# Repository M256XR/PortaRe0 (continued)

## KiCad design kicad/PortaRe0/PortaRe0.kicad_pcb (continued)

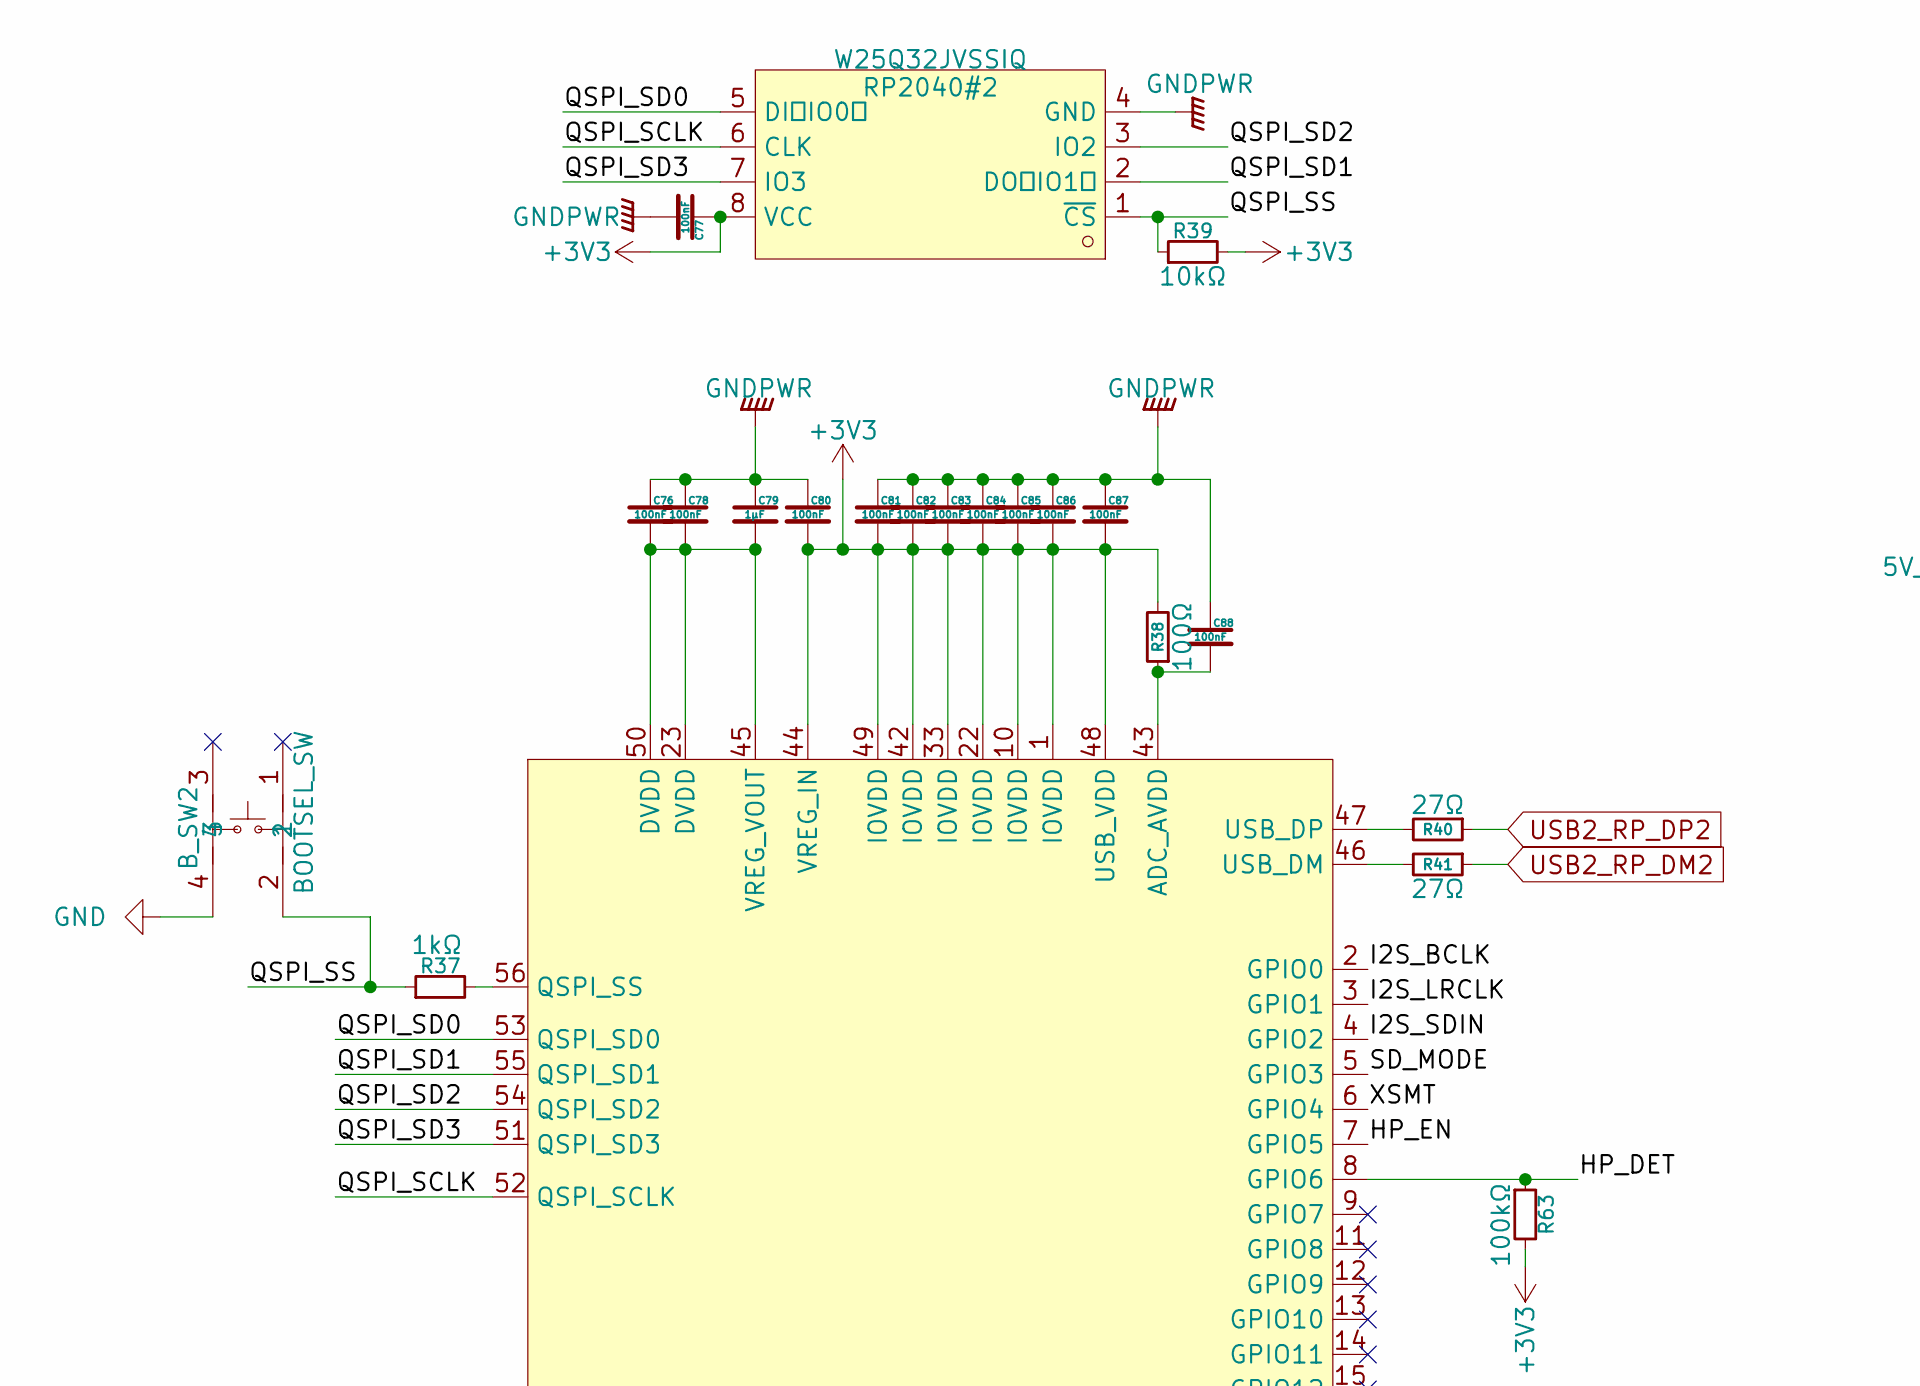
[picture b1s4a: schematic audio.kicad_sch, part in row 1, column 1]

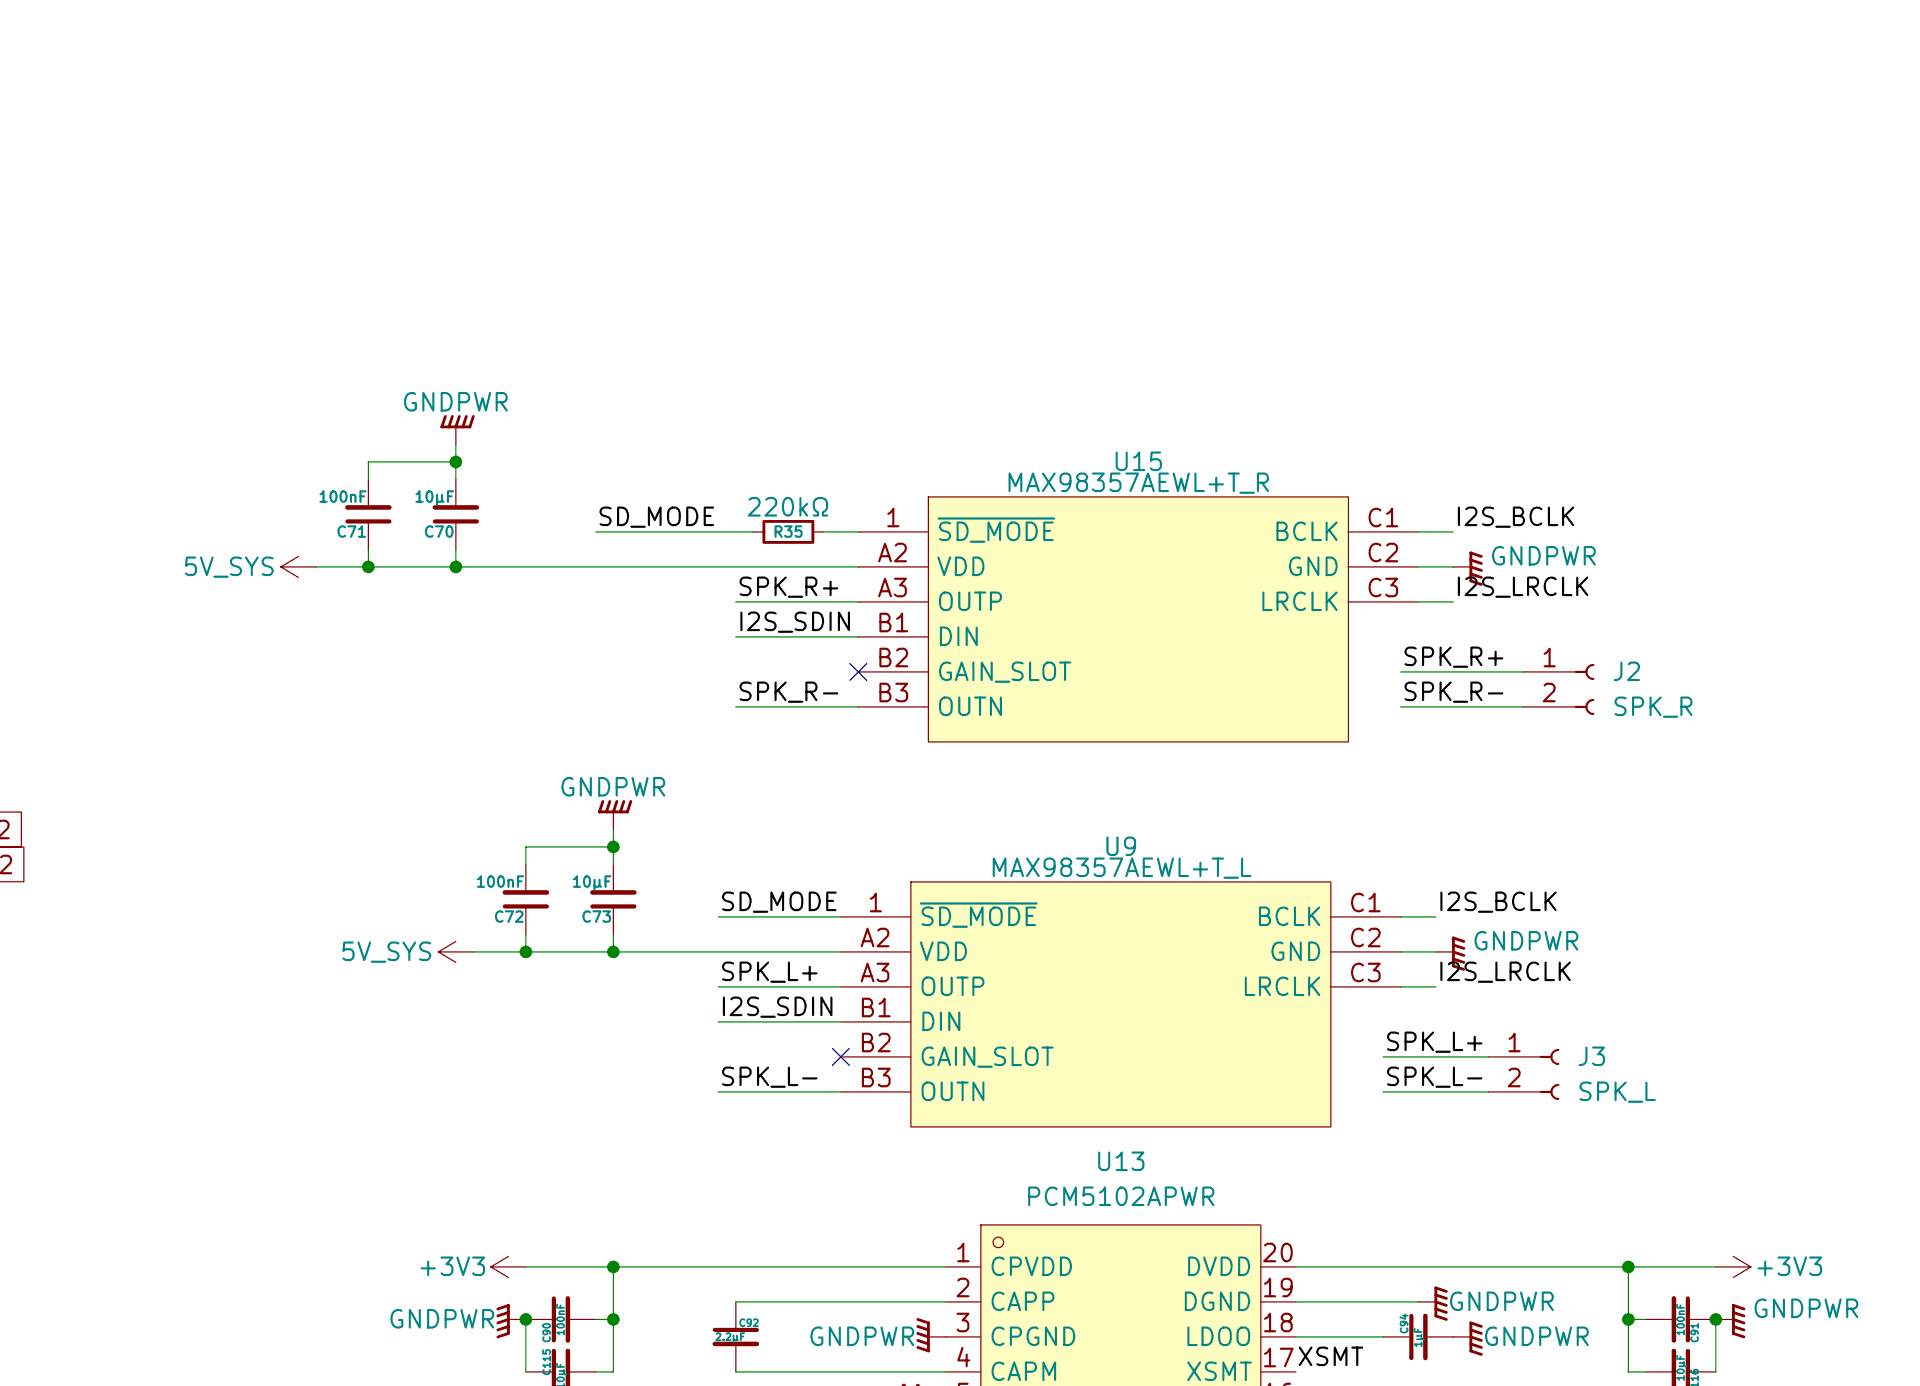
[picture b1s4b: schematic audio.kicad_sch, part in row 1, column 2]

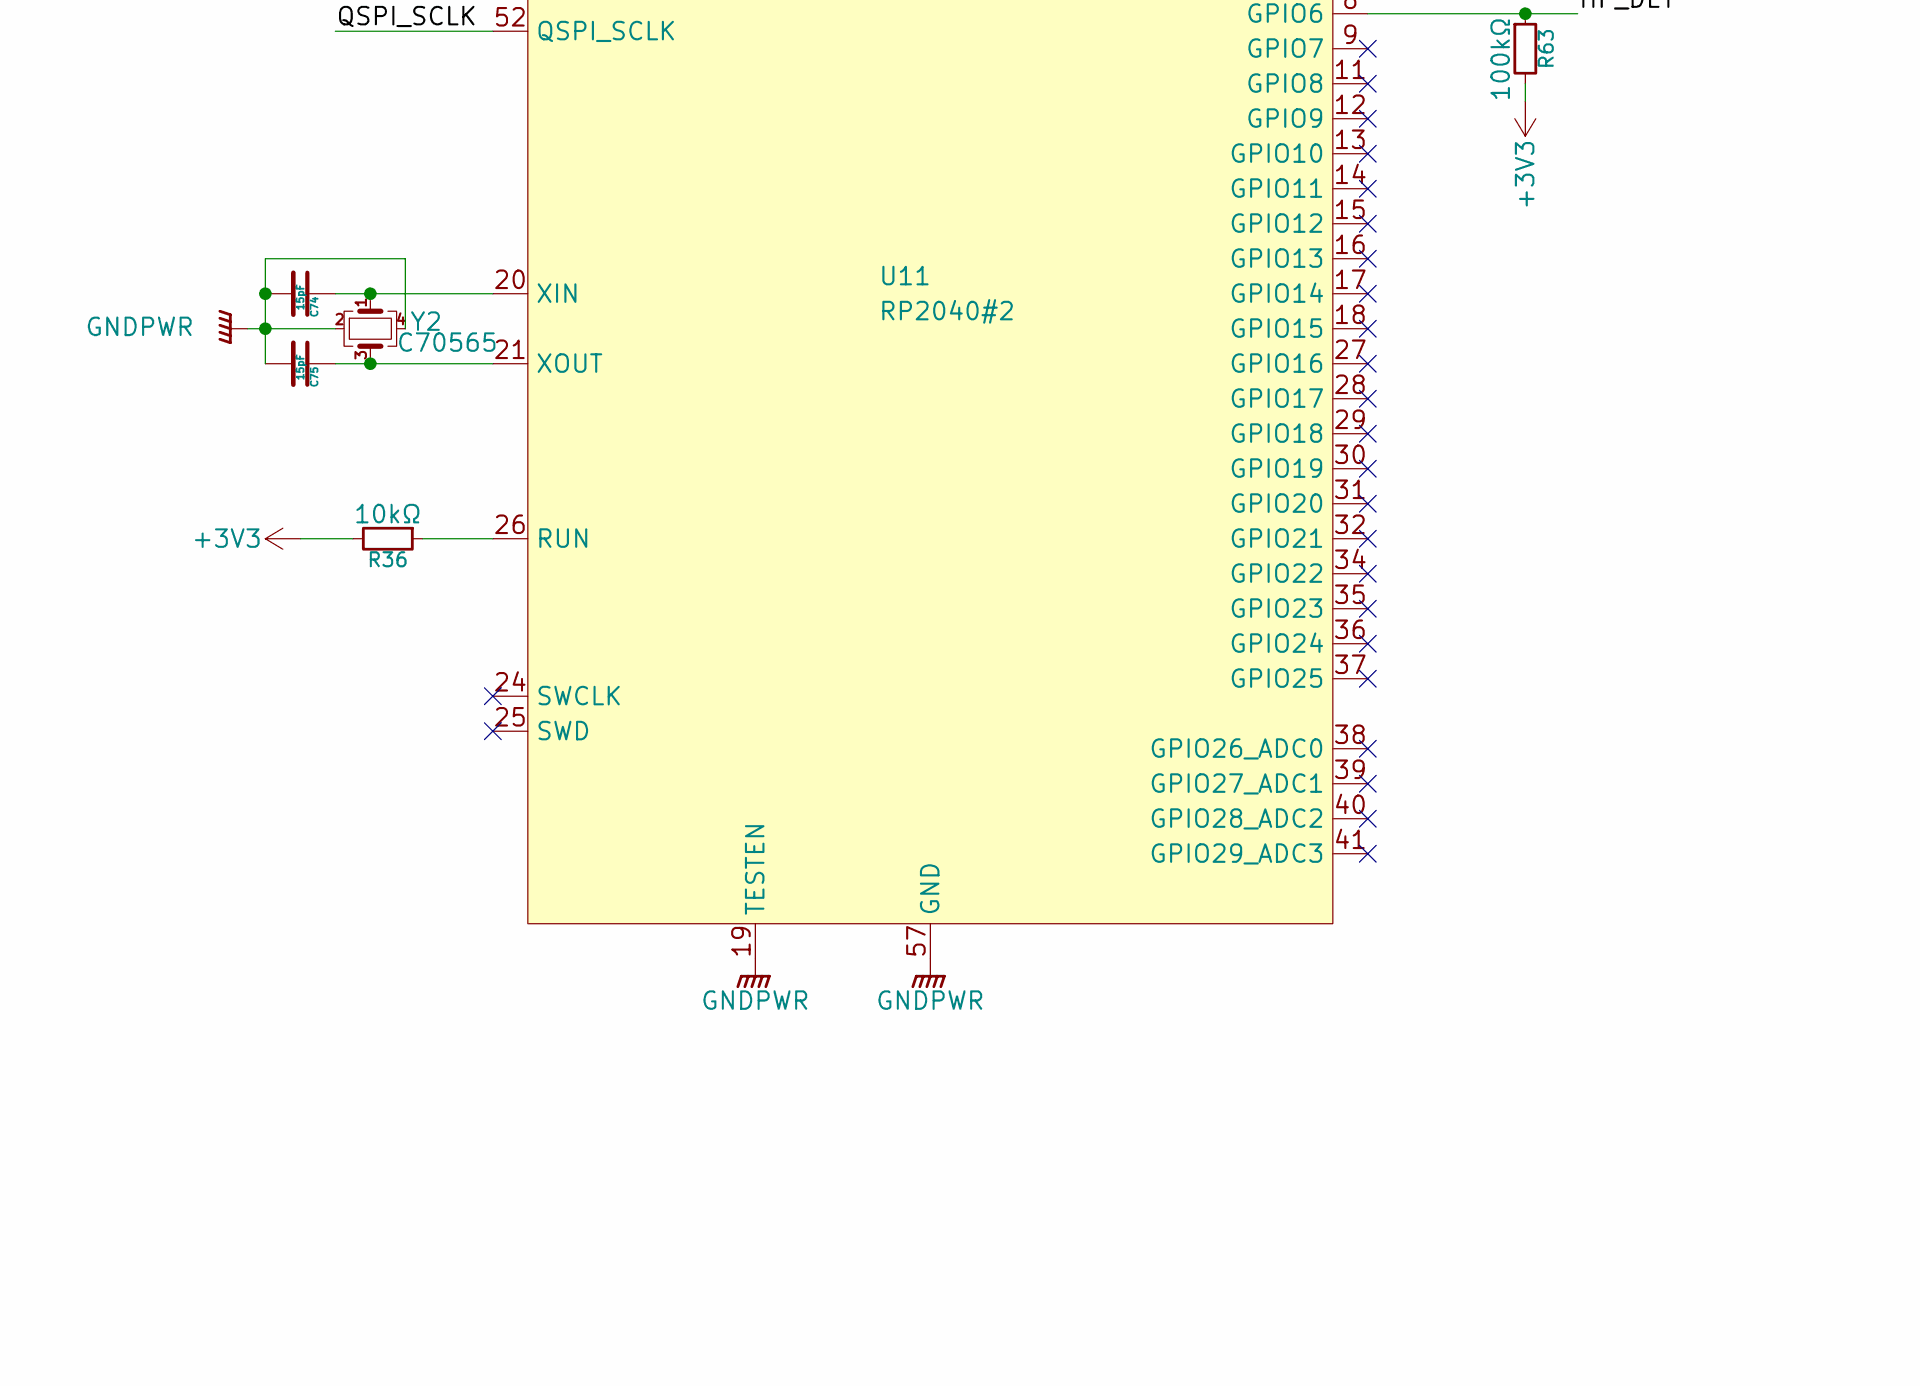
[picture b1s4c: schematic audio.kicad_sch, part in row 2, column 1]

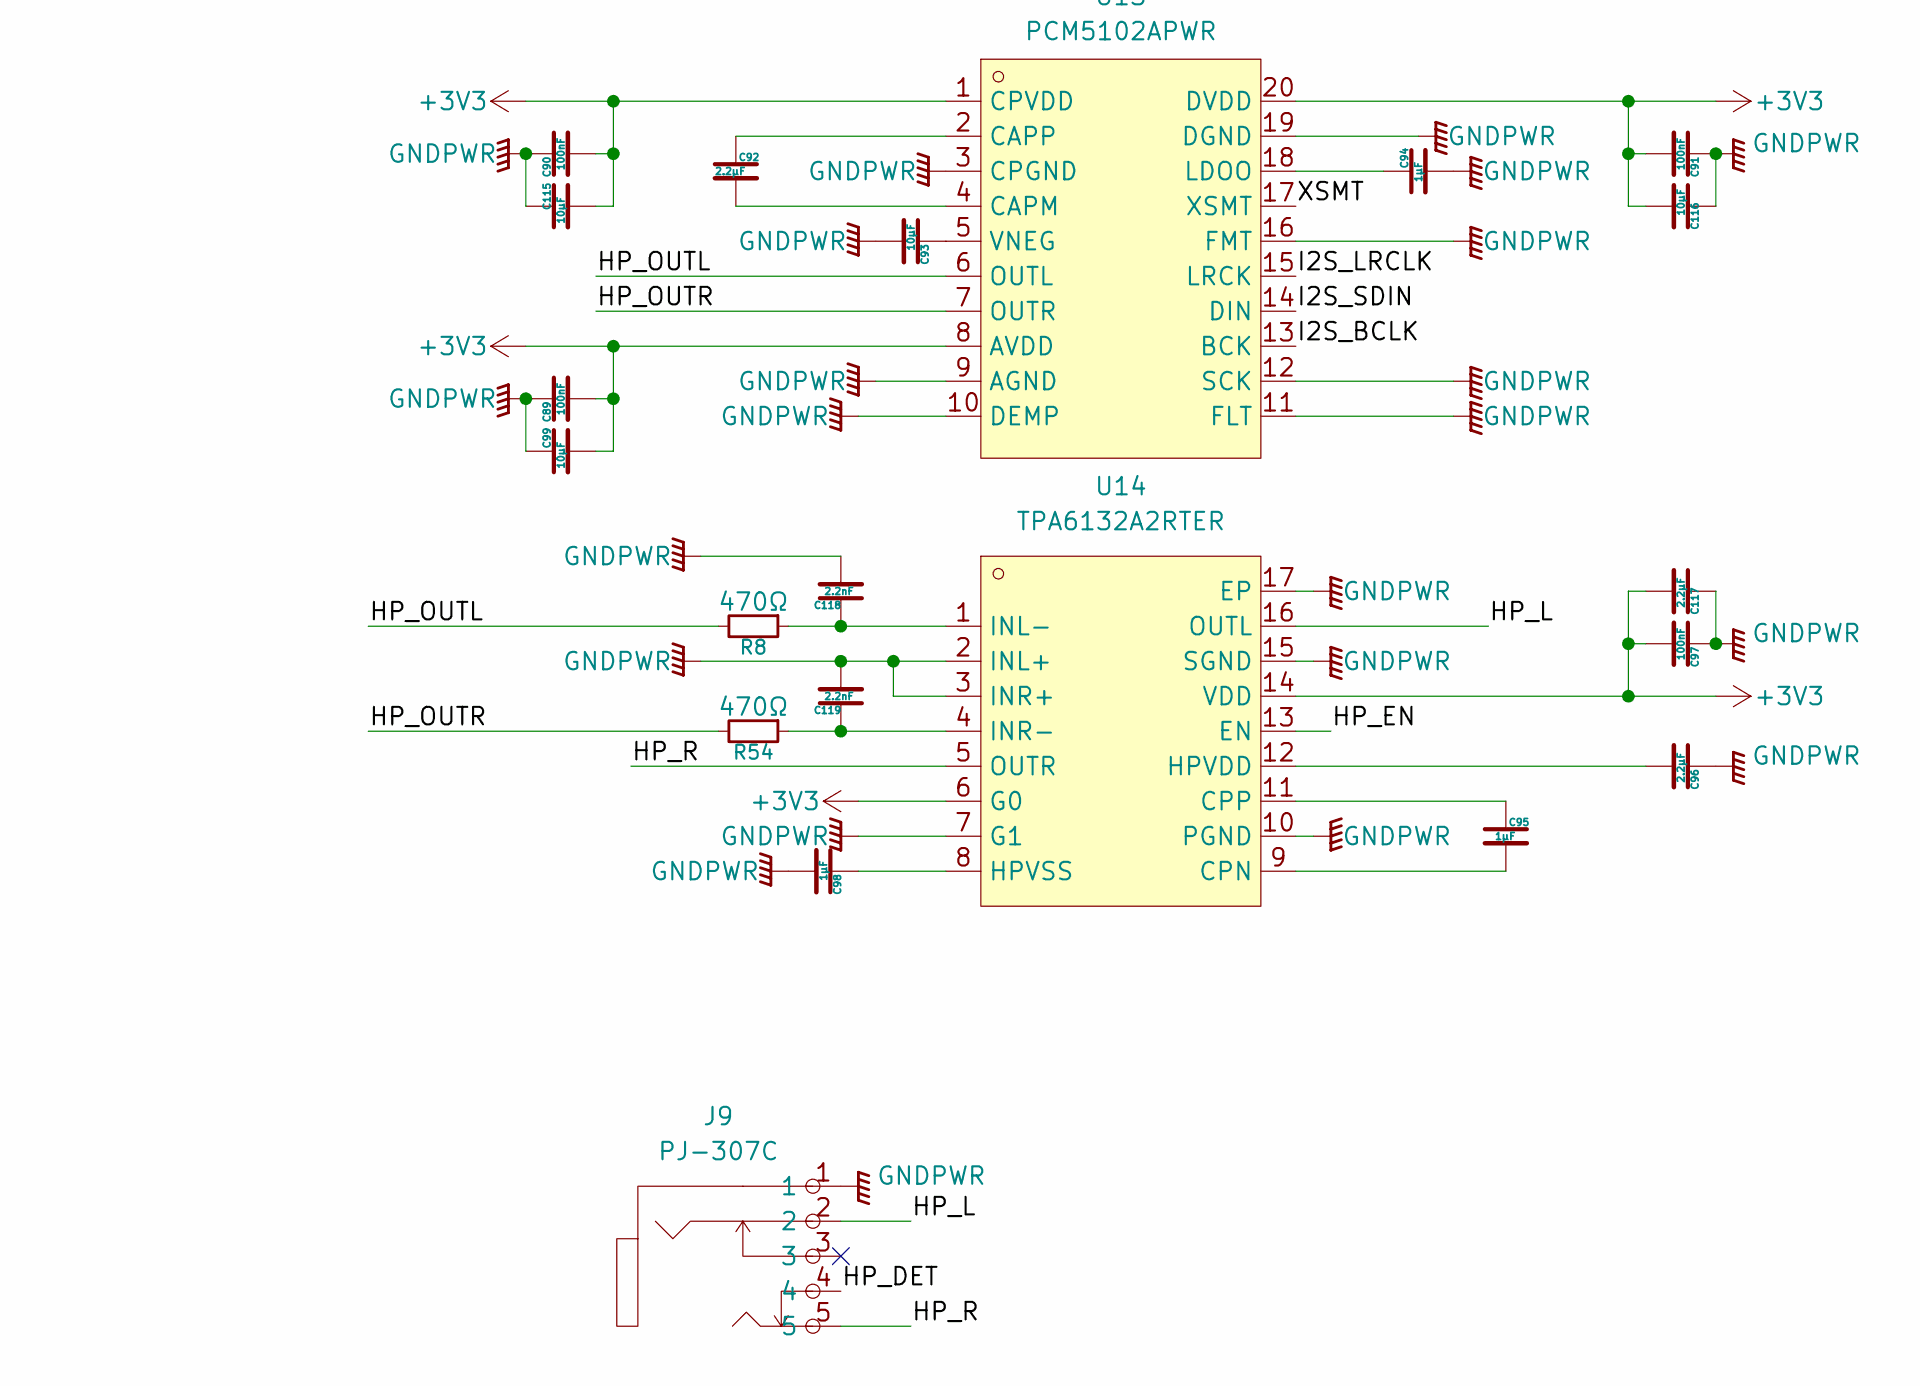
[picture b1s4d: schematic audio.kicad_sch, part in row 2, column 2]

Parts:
B_SW2: BOOTSEL_SW; KEY-SMD_4P-L4.2-W3.2-P2.20-LS4.6; LCSC Part C115360
C70, C73: 10μF; C_0603_1608Metric
C71, C72, C76, C77, C78, C80, C81, C82, C83, C84, C85, C86, C87, C88, C89, C90, C91, C97: 100nF; C_0402_1005Metric
C74, C75: 15pF; C_0402_1005Metric
C79, C94, C95, C98: 1μF; C_0402_1005Metric
C92, C96, C117: 2.2μF; C_0402_1005Metric
C93, C99, C115, C116: 10μF; C_0402_1005Metric
C118, C119: 2.2nF; C_0402_1005Metric
J2: SPK_R; CONN-TH_S2B-PH-K-S-LF-SN
J3: SPK_L; CONN-TH_S2B-PH-K-S-LF-SN
J9: PJ-307C; AUDIO-TH_PJ307C; LCSC Part C16684
R8, R54: 470Ω; R_0402_1005Metric
R35: 220kΩ; R_0603_1608Metric
R36, R39: 10kΩ; R_0402_1005Metric
R37: 1kΩ; R_0402_1005Metric
R38: 100Ω; R_0402_1005Metric
R40, R41: 27Ω; R_0603_1608Metric
R63: 100kΩ; R_0402_1005Metric
RP2040#2: W25Q32JVSSIQ; SOIC-8_L5.3-W5.3-P1.27-LS8.0-BL; LCSC Part C82344
U9: MAX98357AEWL+T_L; WLP-9_L1.4-W1.3-P0.40-R3-C3-BR; LCSC Part C2682619
U11: RP2040#2; LQFN-56_L7.0-W7.0-P0.4-EP; LCSC Part C2040
U13: PCM5102APWR; TSSOP-20_L6.5-W4.4-P0.65-LS6.4-BL; LCSC Part C107671
U14: TPA6132A2RTER; WQFN-16_L3.0-W3.0-P0.50-TL-EP1.6; LCSC Part C69901
U15: MAX98357AEWL+T_R; WLP-9_L1.4-W1.3-P0.40-R3-C3-BR; LCSC Part C2682619
Y2: C70565; CRYSTAL-SMD_4P-L3.2-W2.5-BL

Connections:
5V_SYS: C70.1, C71.1, C72.1, C73.1, U9.A2 (VDD), U15.A2 (VDD); also elsewhere on the board
+3V3: C77.1, C80.2, C81.2, C82.2, C83.2, C84.2, C85.2, C86.2, C87.2, C89.2, C90.2, C91.2, C97.2, C99.2, C115.2, C116.2, C117.2, R36.2, R38.2, R39.2, R63.2, RP2040#2.8 (VCC), U11.1 (IOVDD), U11.10 (IOVDD), U11.22 (IOVDD), U11.33 (IOVDD), U11.42 (IOVDD), U11.44 (VREG_IN), U11.48 (USB_VDD), U11.49 (IOVDD), U13.1 (CPVDD), U13.8 (AVDD), U13.20 (DVDD), U14.6 (G0), U14.14 (VDD); also elsewhere on the board
/audio/HP_DET: J9.4, R63.1, U11.8 (GPIO6)
/audio/HP_EN: U11.7 (GPIO5), U14.13 (EN)
/audio/HP_L: J9.2, U14.16 (OUTL)
/audio/HP_OUTL: R8.2, U13.6 (OUTL)
/audio/HP_OUTR: R54.2, U13.7 (OUTR)
/audio/HP_R: J9.5, U14.5 (OUTR)
/audio/I2S_BCLK: U9.C1 (BCLK), U11.2 (GPIO0), U13.13 (BCK), U15.C1 (BCLK)
/audio/I2S_LRCLK: U9.C3 (LRCLK), U11.3 (GPIO1), U13.15 (LRCK), U15.C3 (LRCLK)
/audio/I2S_SDIN: U9.B1 (DIN), U11.4 (GPIO2), U13.14 (DIN), U15.B1 (DIN)
/audio/QSPI_SCLK: RP2040#2.6 (CLK), U11.52 (QSPI_SCLK)
/audio/QSPI_SD0: RP2040#2.5 (DI（IO0）), U11.53 (QSPI_SD0)
/audio/QSPI_SD1: RP2040#2.2 (DO（IO1）), U11.55 (QSPI_SD1)
/audio/QSPI_SD2: RP2040#2.3 (IO2), U11.54 (QSPI_SD2)
/audio/QSPI_SD3: RP2040#2.7 (IO3), U11.51 (QSPI_SD3)
/audio/QSPI_SS: B_SW2.2, R37.1, R39.1, RP2040#2.1 (~CS)
/audio/SD_MODE: R35.2, U9.1 (~SD_MODE), U11.5 (GPIO3)
/audio/SPK_L+: J3.1, U9.A3 (OUTP); also elsewhere on the board
/audio/SPK_L-: J3.2, U9.B3 (OUTN); also elsewhere on the board
/audio/SPK_R+: J2.1, U15.A3 (OUTP); also elsewhere on the board
/audio/SPK_R-: J2.2, U15.B3 (OUTN); also elsewhere on the board
/audio/XSMT: U11.6 (GPIO4), U13.17 (XSMT)
GND: B_SW2.4, C70.2, C71.2, C72.2, C73.2, C74.2, C75.2, C76.1, C77.2, C78.1, C79.1, C80.1, C81.1, C82.1, C83.1, C84.1, C85.1, C86.1, C87.1, C88.1, C89.1, C90.1, C91.1, C93.2, C94.2, C96.1, C97.1, C98.2, C99.1, C115.1, C116.1, C117.1, C118.2, C119.2, J9.1, RP2040#2.4 (GND), U9.C2 (GND), U11.19 (TESTEN), U11.57 (GND), U13.3 (CPGND), U13.9 (AGND), U13.10 (DEMP), U13.11 (FLT), U13.12 (SCK), U13.16 (FMT), U13.19 (DGND), U14.2 (INL+), U14.3 (INR+), U14.7 (G1), U14.10 (PGND), U14.15 (SGND), U14.17 (EP), U15.C2 (GND), Y2.2, Y2.4; also elsewhere on the board
unnamed: C88.2, R38.1, U11.43 (ADC_AVDD)
unnamed: R37.2, U11.56 (QSPI_SS)
unnamed: R36.1, U11.26 (RUN)
unnamed: R41.2, U11.46 (USB_DM)
unnamed: R40.2, U11.47 (USB_DP)
unnamed: C76.2, C78.2, C79.2, U11.23 (DVDD), U11.45 (VREG_VOUT), U11.50 (DVDD)
unnamed: C74.1, U11.20 (XIN), Y2.1
unnamed: C75.1, U11.21 (XOUT), Y2.3
unnamed: C92.2, U13.4 (CAPM)
unnamed: C92.1, U13.2 (CAPP)
unnamed: C94.1, U13.18 (LDOO)
unnamed: C93.1, U13.5 (VNEG)
unnamed: C95.2, U14.9 (CPN)
unnamed: C95.1, U14.11 (CPP)
unnamed: C96.2, U14.12 (HPVDD)
unnamed: C98.1, U14.8 (HPVSS)
unnamed: C118.1, R8.1, U14.1 (INL-)
unnamed: C119.1, R54.1, U14.4 (INR-)
unnamed: R35.1, U15.1 (~SD_MODE)
USB2_RP_DM2: R41.1; also elsewhere on the board
USB2_RP_DP2: R40.1; also elsewhere on the board

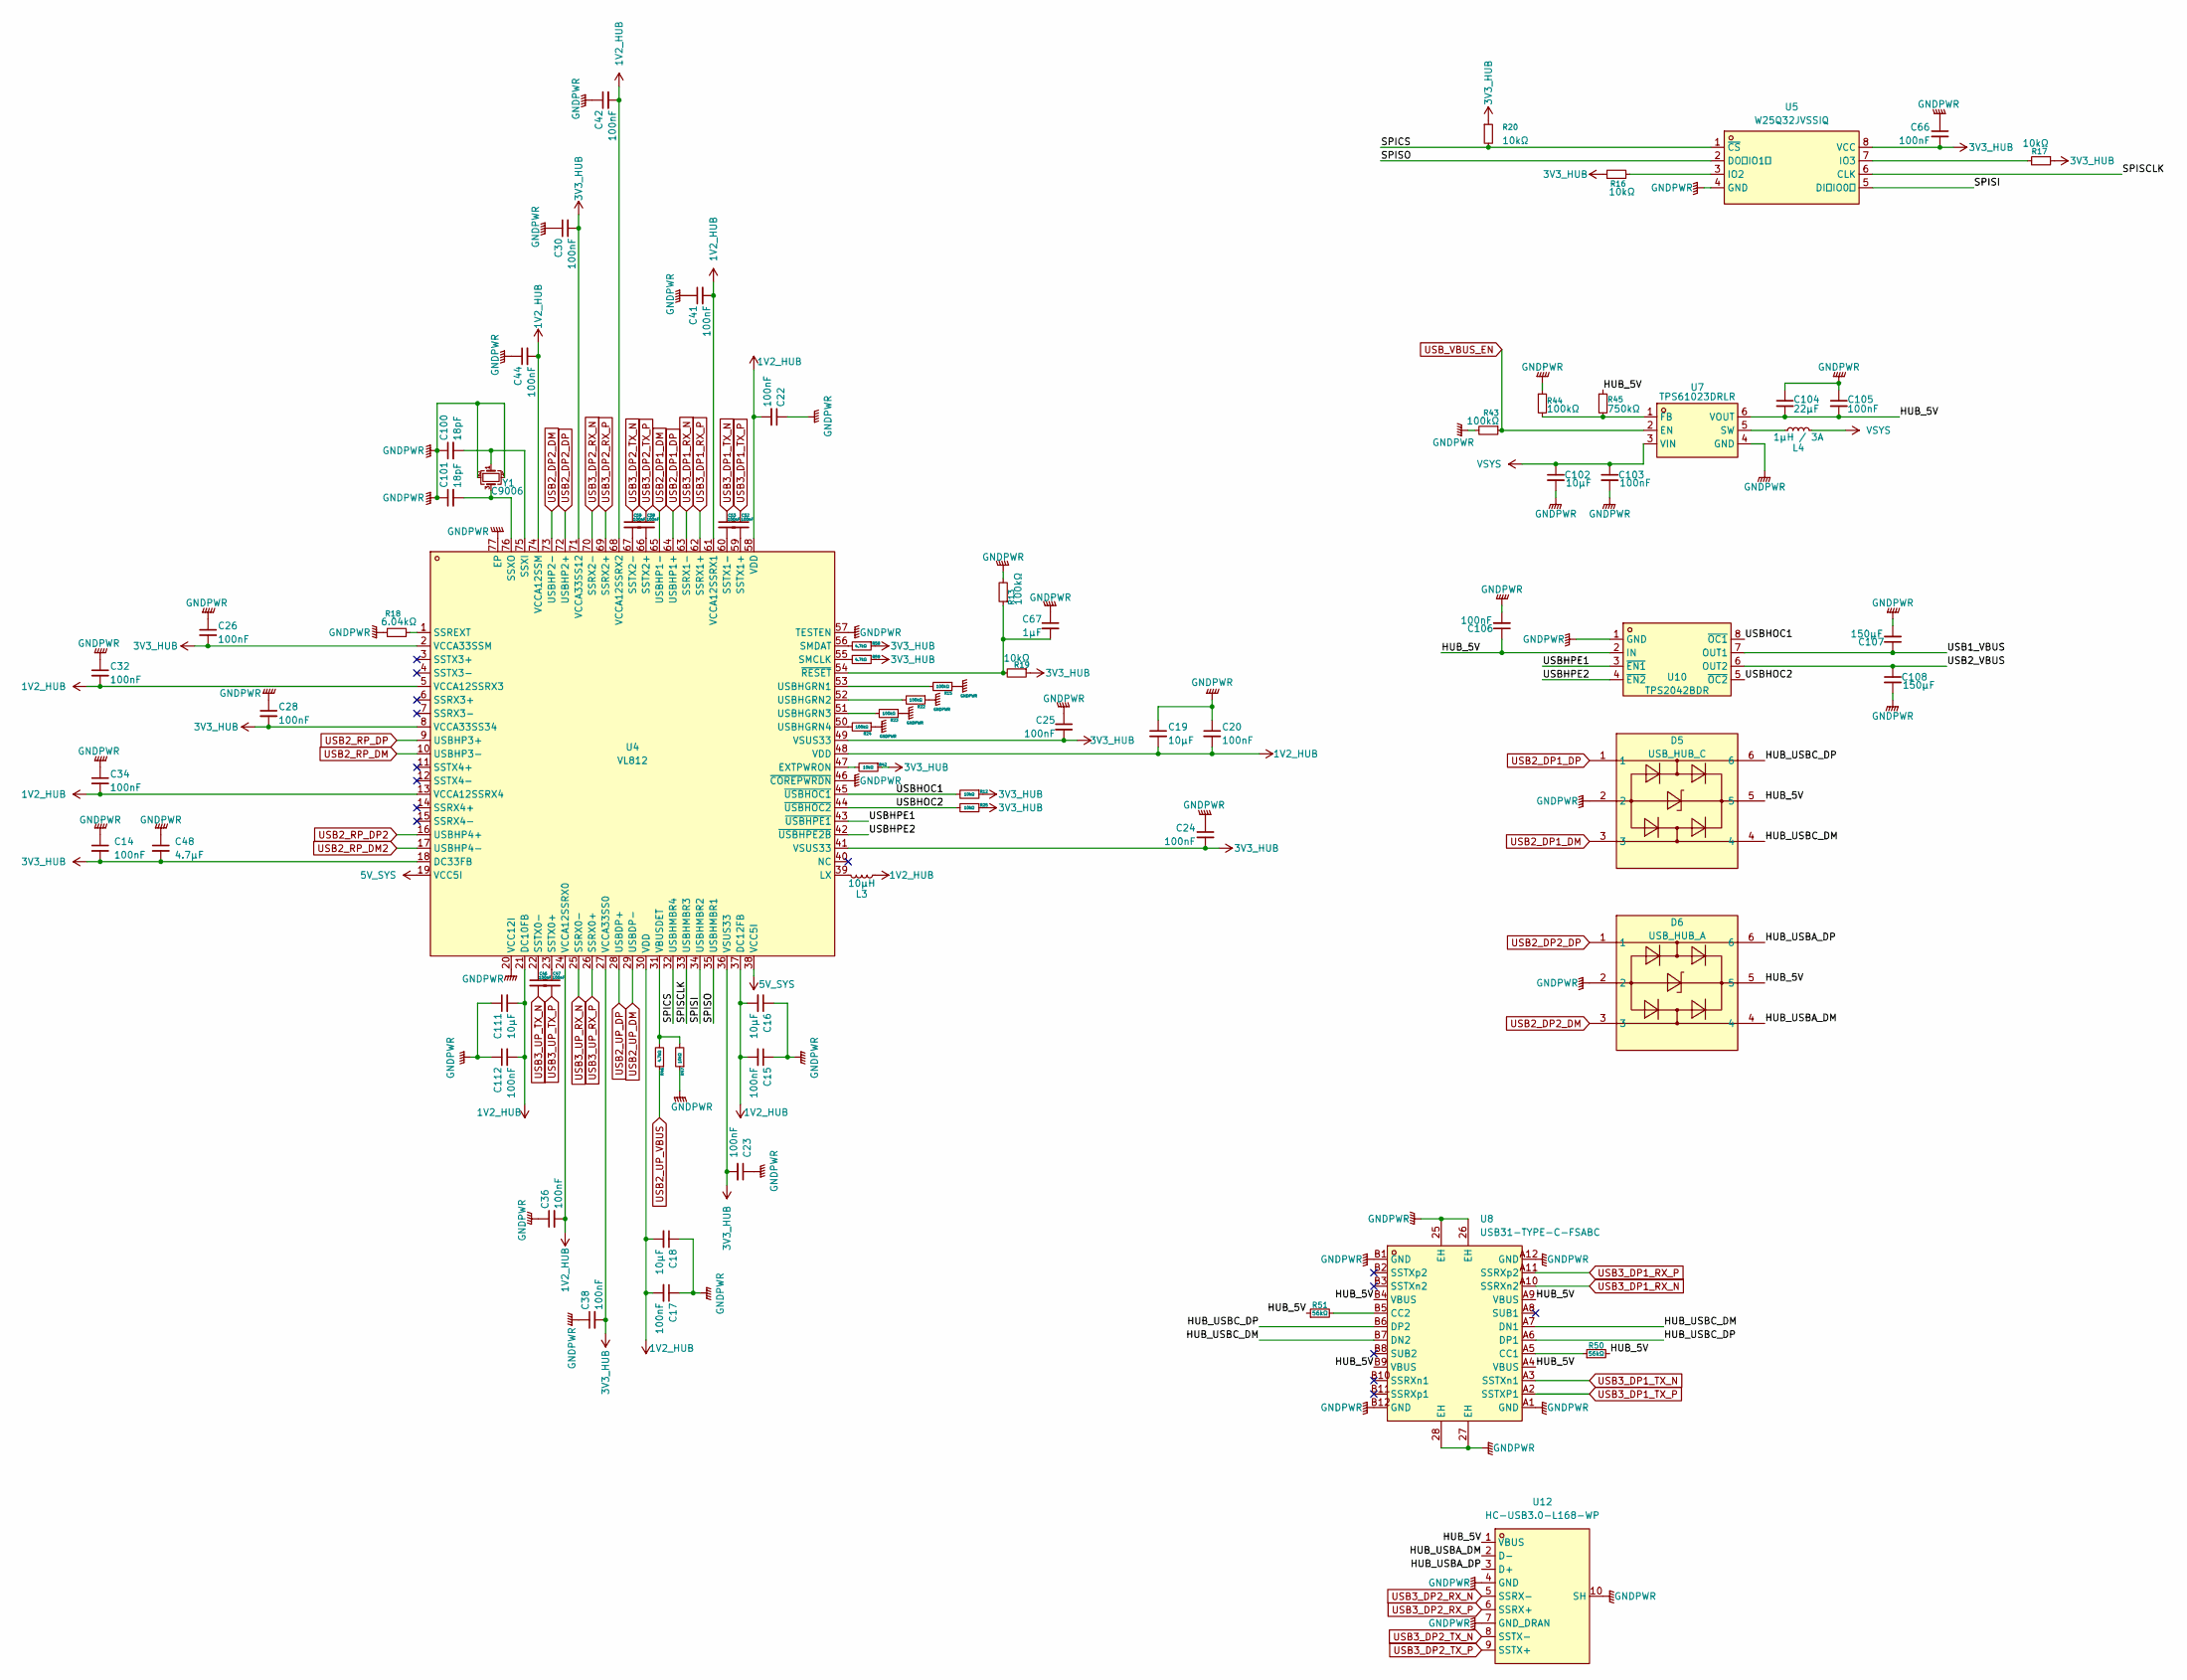
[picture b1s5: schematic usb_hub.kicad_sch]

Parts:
C14, C15, C17, C20, C22, C23, C24, C25, C26, C28, C30, C32, C34, C36, C38, C41, C42, C44, C46, C47, C52, C53, C58, C59, C66, C103, C105, C106, C112: 100nF; C_0402_1005Metric
C16, C18, C19, C111: 10μF; C_0402_1005Metric
C48: 4.7μF; C_0402_1005Metric
C67: 1μF; C_0402_1005Metric
C100, C101: 18pF; C_0402_1005Metric
C102: 10μF; C_0603_1608Metric
C104: 22μF; C_0603_1608Metric
C107, C108: 150μF; CP_EIA-3528-21_Kemet-B_HandSolder
D5: USB_HUB_C; SOT-23-6_L2.9-W1.6-P0.95-LS2.8-BL; LCSC Part C7519
D6: USB_HUB_A; SOT-23-6_L2.9-W1.6-P0.95-LS2.8-BL; LCSC Part C7519
L3: 10μH; IND-SMD_L4.7-W4.2
L4: 1µH / 3A; IND-SMD_L3.2-W2.5_CKST322512-2.2UH
R12, R16, R17, R19, R20, R25, R42, R47: 10kΩ; R_0402_1005Metric
R13, R15, R22, R23, R24, R43, R44: 100kΩ; R_0402_1005Metric
R18: 6.04kΩ; R_0603_1608Metric
R45: 750kΩ; R_0603_1608Metric
R46, R58, R59: 4.7kΩ; R_0402_1005Metric
R50, R51: 56kΩ; R_0603_1608Metric
U4: VL812; QFN-76_L9.0-W9.0-P0.40-BL-EP; LCSC Part C69417
U5: W25Q32JVSSIQ; SOIC-8_L5.3-W5.3-P1.27-LS8.0-BL; LCSC Part C82344
U7: TPS61023DRLR; SOT-563_L1.6-W1.2-P0.50-LS1.6-BR; LCSC Part C919459
U8: USB31-TYPE-C-FSABC; USB-C-SMD_USB31-TYPE-C-FSABC; LCSC Part C2880583
U10: TPS2042BDR; SOIC-8_L4.9-W3.9-P1.27-LS6.0-BL; LCSC Part C138720
U12: HC-USB3.0-L168-WP; USB-TH_USB3.0-A; LCSC Part C7501850
Y1: C9006; CRYSTAL-SMD_4P-L3.2-W2.5-BL

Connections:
1V2_HUB: C15.2, C16.2, C17.2, C18.2, C19.2, C20.2, C22.2, C32.2, C34.2, C36.2, C41.2, C42.2, C44.2, C111.2, C112.2, L3.1, U4.5 (VCCA12SSRX3), U4.13 (VCCA12SSRX4), U4.21 (DC10FB), U4.24 (VCCA12SSRX0), U4.30 (VDD), U4.37 (DC12FB), U4.48 (VDD), U4.58 (VDD), U4.61 (VCCA12SSRX1), U4.68 (VCCA12SSRX2), U4.74 (VCCA12SSM)
3V3_HUB: C14.2, C23.2, C24.2, C25.2, C26.2, C28.2, C30.2, C38.2, C48.2, C66.2, R12.1, R16.1, R17.1, R19.1, R20.1, R25.1, R42.1, R58.1, R59.1, U4.2 (VCCA33SSM), U4.8 (VCCA33SS34), U4.18 (DC33FB), U4.27 (VCCA33SS0), U4.36 (VSUS33), U4.41 (VSUS33), U4.49 (VSUS33), U4.71 (VCCA33SS12), U5.8 (VCC)
5V_SYS: U4.19 (VCC5I), U4.38 (VCC5I); also elsewhere on the board
/usb_hub/HUB_5V: C104.2, C105.2, C106.1, D5.5, D6.5, R45.1, R50.2, R51.1, U7.6 (VOUT), U8.A4 (VBUS), U8.A9 (VBUS), U8.B4 (VBUS), U8.B9 (VBUS), U10.2 (IN), U12.1 (VBUS)
/usb_hub/HUB_USBA_DM: D6.4, U12.2 (D-)
/usb_hub/HUB_USBA_DP: D6.6, U12.3 (D+)
/usb_hub/HUB_USBC_DM: D5.4, U8.A7 (DN1), U8.B7 (DN2)
/usb_hub/HUB_USBC_DP: D5.6, U8.A6 (DP1), U8.B6 (DP2)
/usb_hub/SPICS: R20.2, U4.32 (USBHMBR4), U5.1 (~CS)
/usb_hub/SPISCLK: U4.33 (USBHMBR3), U5.6 (CLK)
/usb_hub/SPISI: U4.34 (USBHMBR2), U5.5 (DI（IO0）)
/usb_hub/SPISO: U4.35 (USBHMBR1), U5.2 (DO（IO1）)
/usb_hub/USB1_VBUS: C107.1, U10.7 (OUT1)
/usb_hub/USB2_VBUS: C108.1, U10.6 (OUT2)
/usb_hub/USBHOC1: R12.2, U4.45 (~USBHOC1), U10.8 (~OC1)
/usb_hub/USBHOC2: R25.2, U4.44 (~USBHOC2), U10.5 (~OC2)
/usb_hub/USBHPE1: U4.43 (~USBHPE1), U10.3 (~EN1)
/usb_hub/USBHPE2: U4.42 (~USBHPE2B), U10.4 (~EN2)
GND: C14.1, C15.1, C16.1, C17.1, C18.1, C19.1, C20.1, C22.1, C23.1, C24.1, C25.1, C26.1, C28.1, C30.1, C32.1, C34.1, C36.1, C38.1, C41.1, C42.1, C44.1, C48.1, C66.1, C67.1, C100.1, C101.1, C102.2, C103.2, C104.1, C105.1, C106.2, C107.2, C108.2, C111.1, C112.1, D5.2, D6.2, R13.2, R15.1, R18.1, R22.1, R23.1, R24.1, R43.2, R44.1, R47.1, U4.20 (VCC12I), U4.46 (~COREPWRDN), U4.57 (TESTEN), U4.77 (EP), U5.4 (GND), U7.4 (GND), U8.25 (EH), U8.26 (EH), U8.27 (EH), U8.28 (EH), U8.A1 (GND), U8.A12 (GND), U8.B1 (GND), U8.B12 (GND), U10.1 (GND), U12.4 (GND), U12.7 (GND_DRAN), U12.10 (SH), Y1.2, Y1.4; also elsewhere on the board
unnamed: R42.2, U4.47 (EXTPWRON)
unnamed: L3.2, U4.39 (LX)
unnamed: R59.2, U4.55 (SMCLK)
unnamed: R58.2, U4.56 (SMDAT)
unnamed: R18.2, U4.1 (SSREXT)
unnamed: C47.1, U4.23 (SSTX0+)
unnamed: C46.1, U4.22 (SSTX0-)
unnamed: C52.2, U4.59 (SSTX1+)
unnamed: C53.2, U4.60 (SSTX1-)
unnamed: C58.2, U4.66 (SSTX2+)
unnamed: C59.2, U4.67 (SSTX2-)
unnamed: C100.2, U4.75 (SSXI), Y1.1
unnamed: C101.2, U4.76 (SSXO), Y1.3
unnamed: R15.2, U4.53 (USBHGRN1)
unnamed: R22.2, U4.52 (USBHGRN2)
unnamed: R23.2, U4.51 (USBHGRN3)
unnamed: R24.2, U4.50 (USBHGRN4)
unnamed: R46.2, R47.2, U4.31 (VBUSDET)
unnamed: C67.2, R13.1, R19.2, U4.54 (~RESET)
unnamed: R16.2, U5.3 (IO2)
unnamed: R17.2, U5.7 (IO3)
unnamed: R44.2, R45.2, U7.1 (FB)
unnamed: L4.1, U7.5 (SW)
unnamed: R50.1, U8.A5 (CC1)
unnamed: R51.2, U8.B5 (CC2)
USB2_DP1_DM: D5.3, U4.65 (USBHP1-)
USB2_DP1_DP: D5.1, U4.64 (USBHP1+)
USB2_DP2_DM: D6.3, U4.73 (USBHP2-)
USB2_DP2_DP: D6.1, U4.72 (USBHP2+)
USB2_RP_DM: U4.10 (USBHP3-); also elsewhere on the board
USB2_RP_DM2: U4.17 (USBHP4-); also elsewhere on the board
USB2_RP_DP: U4.9 (USBHP3+); also elsewhere on the board
USB2_RP_DP2: U4.16 (USBHP4+); also elsewhere on the board
USB2_UP_DM: U4.29 (USBDP-); also elsewhere on the board
USB2_UP_DP: U4.28 (USBDP+); also elsewhere on the board
USB2_UP_VBUS: R46.1; also elsewhere on the board
USB3_DP1_RX_N: U4.63 (SSRX1-), U8.A10 (SSRXn2)
USB3_DP1_RX_P: U4.62 (SSRX1+), U8.A11 (SSRXp2)
USB3_DP1_TX_N: C53.1, U8.A3 (SSTXn1)
USB3_DP1_TX_P: C52.1, U8.A2 (SSTXP1)
USB3_DP2_RX_N: U4.70 (SSRX2-), U12.5 (SSRX-)
USB3_DP2_RX_P: U4.69 (SSRX2+), U12.6 (SSRX+)
USB3_DP2_TX_N: C59.1, U12.8 (SSTX-)
USB3_DP2_TX_P: C58.1, U12.9 (SSTX+)
USB3_UP_RX_N: U4.25 (SSRX0-); also elsewhere on the board
USB3_UP_RX_P: U4.26 (SSRX0+); also elsewhere on the board
USB3_UP_TX_N: C46.2; also elsewhere on the board
USB3_UP_TX_P: C47.2; also elsewhere on the board
USB_VBUS_EN: R43.1, U7.2 (EN); also elsewhere on the board
VSYS: C102.1, C103.1, L4.2, U7.3 (VIN); also elsewhere on the board
